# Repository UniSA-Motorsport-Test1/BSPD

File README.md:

View this project on [CADLAB.io](https://cadlab.io/project/26523). 

# BSPD

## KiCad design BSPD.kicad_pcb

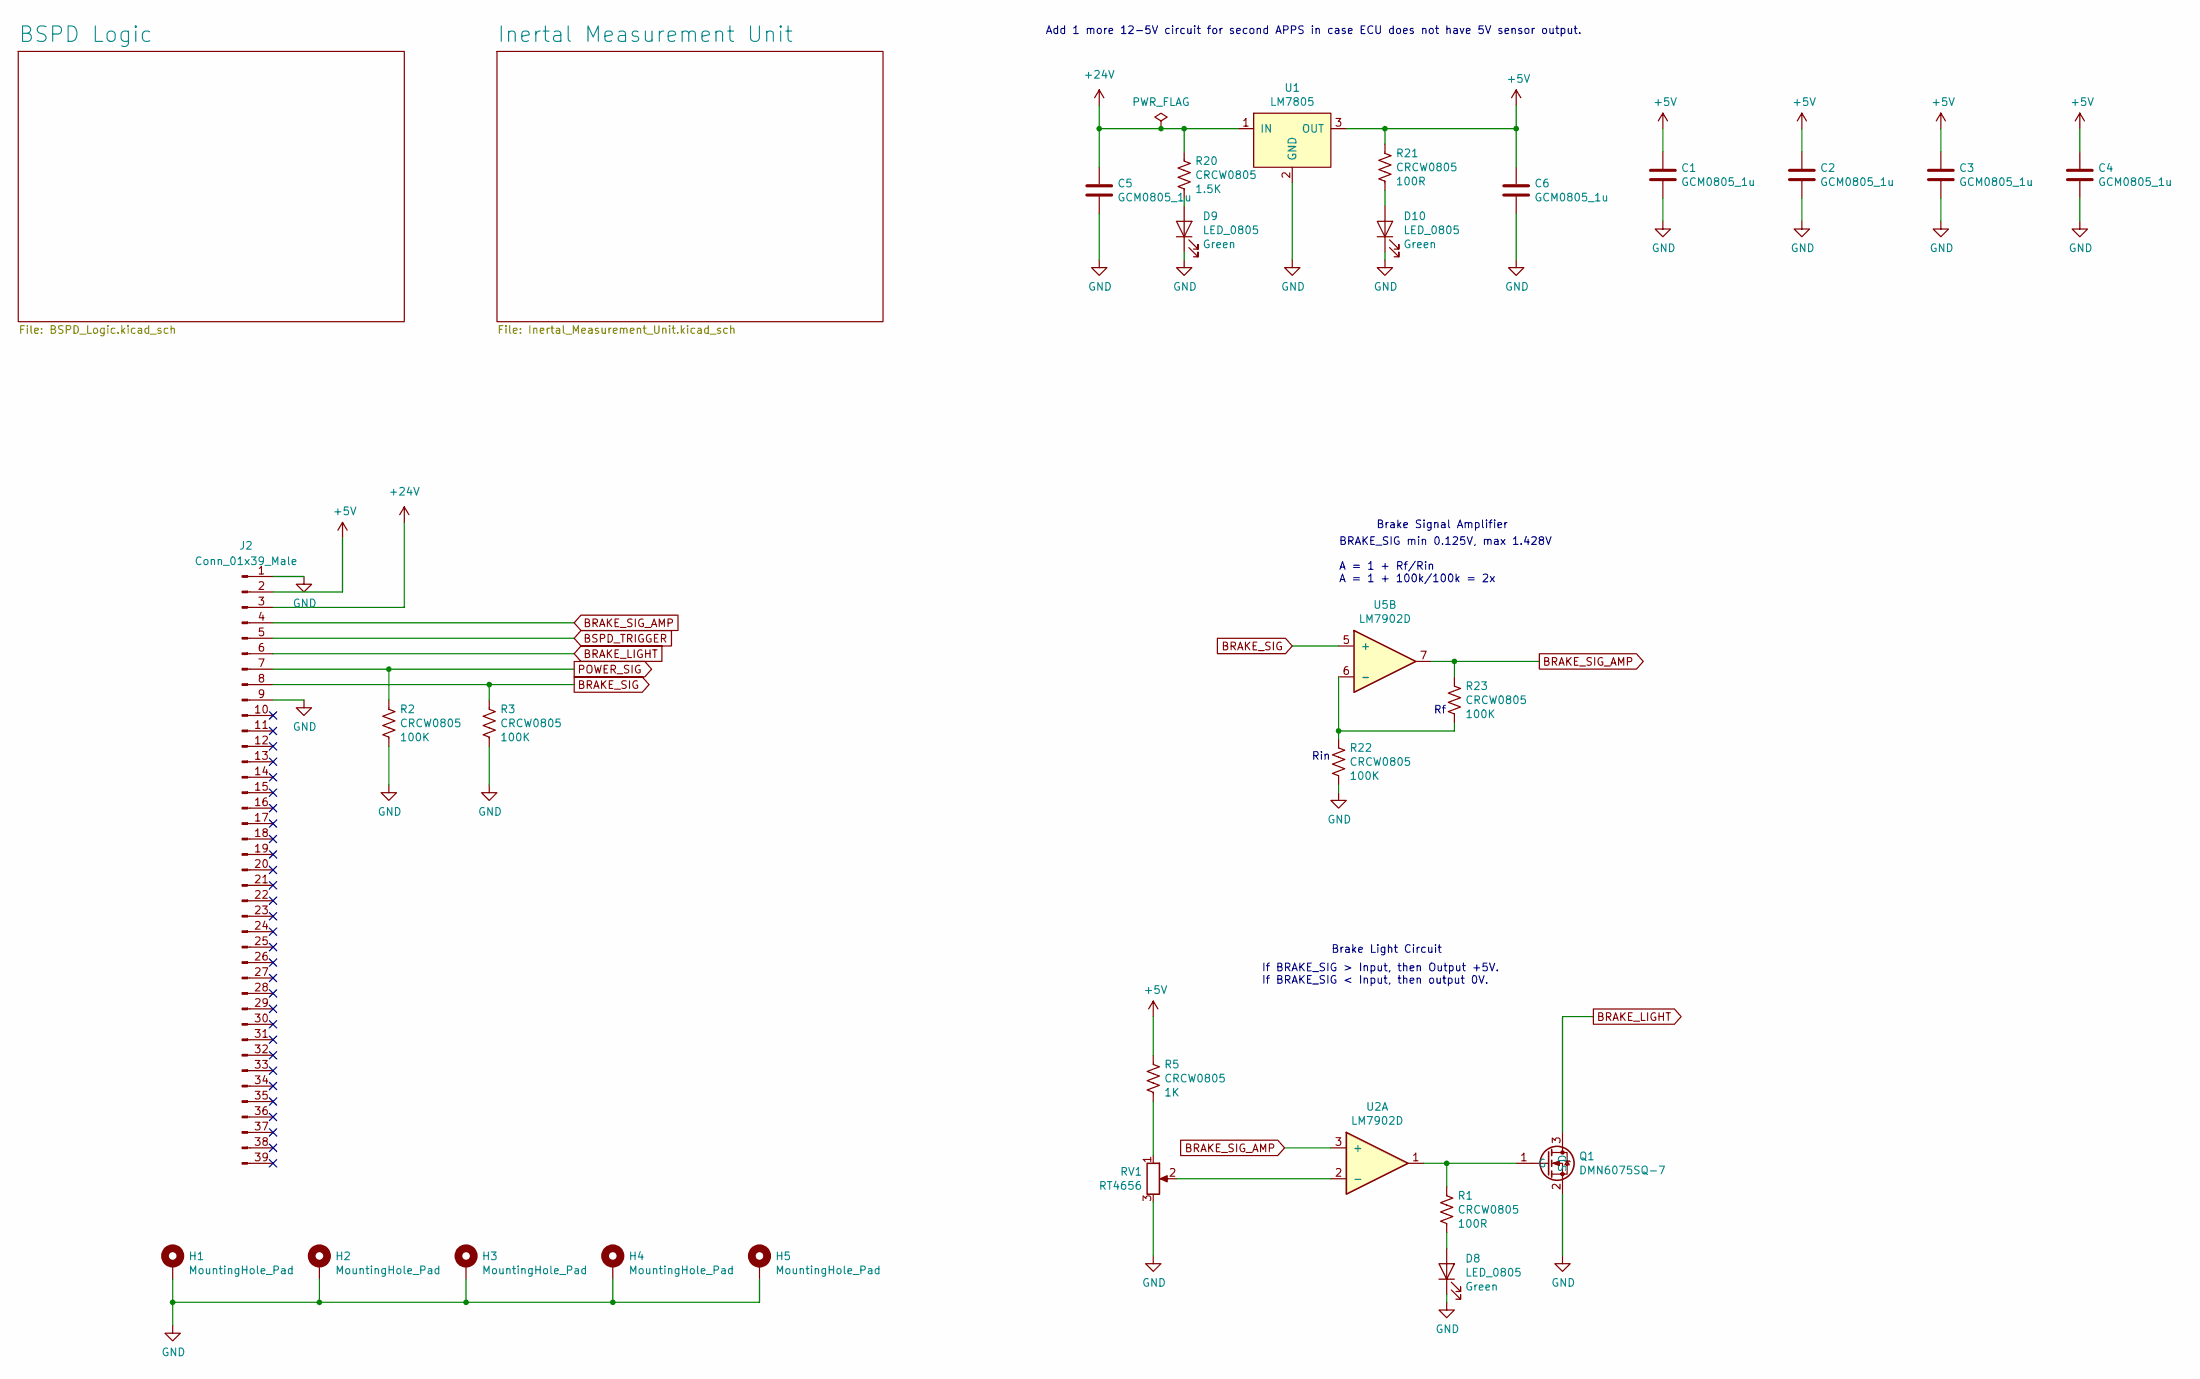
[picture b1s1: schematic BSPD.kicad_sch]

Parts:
C1, C2, C3, C4, C5, C6: GCM0805_1u; 0805; Voltage Rating 50V
D8, D9, D10: LED_0805; 0805
H1, H2, H3, H4, H5: MountingHole_Pad; MountingHole_3.2mm_M3_Pad_Via
J2: Conn_01x39_Male; Samtec_MECF-40-0_-L-DV_2x40_P1.27mm_Polarized_Edge
Q1: DMN6075SQ-7; SOT-23-3
R1, R2, R3, R5, R20, R21, R22, R23: CRCW0805; 0805; Voltage Rating 150V; Power Rating 125mW
RV1: RT4656; PinHeader_1x03_P2.54mm_Vertical
U1: LM7805; SOT-223-4; Current Rating 1.5A
U2, U5: LM7902D; SOIC-14

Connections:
+5V: C1.1, C2.1, C3.1, C4.1, C6.1, J2.2, R5.1, R21.1, U1.3 (OUT); also elsewhere on the board
+24V: C5.1, J2.3, R20.1, U1.1 (IN); also elsewhere on the board
BRAKE_LIGHT: J2.6, Q1.3 (D)
BRAKE_SIG: J2.8, R3.1, U5.5 (+)
BRAKE_SIG_AMP: J2.4, R23.1, U2.3 (+), U5.7; also elsewhere on the board
BSPD_TRIGGER: J2.5; also elsewhere on the board
GND: C1.2, C2.2, C3.2, C4.2, C5.2, C6.2, D8.1 (K), D9.1 (K), D10.1 (K), H1.1, H2.1, H3.1, H4.1, H5.1, J2.1, J2.9, Q1.2 (S), R2.2, R3.2, R22.2, RV1.3, U1.2 (GND); also elsewhere on the board
unnamed: D8.2 (A), R1.2
unnamed: D9.2 (A), R20.2
unnamed: D10.2 (A), R21.2
unnamed: Q1.1 (G), R1.1, U2.1
unnamed: R5.2, RV1.1
unnamed: R22.1, R23.2, U5.6 (-)
unnamed: RV1.2, U2.2 (-)
POWER_SIG: J2.7, R2.1; also elsewhere on the board

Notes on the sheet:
Rin
Brake Signal Amplifier
Add 1 more 12-5V circuit for second APPS in case ECU does not have 5V sensor output.
Brake Light Circuit
BRAKE_SIG min 0.125V, max 1.428V A = 1 + Rf/Rin A = 1 + 100k/100k = 2x
If BRAKE_SIG > Input, then Output +5V. If BRAKE_SIG < Input, then output 0V.

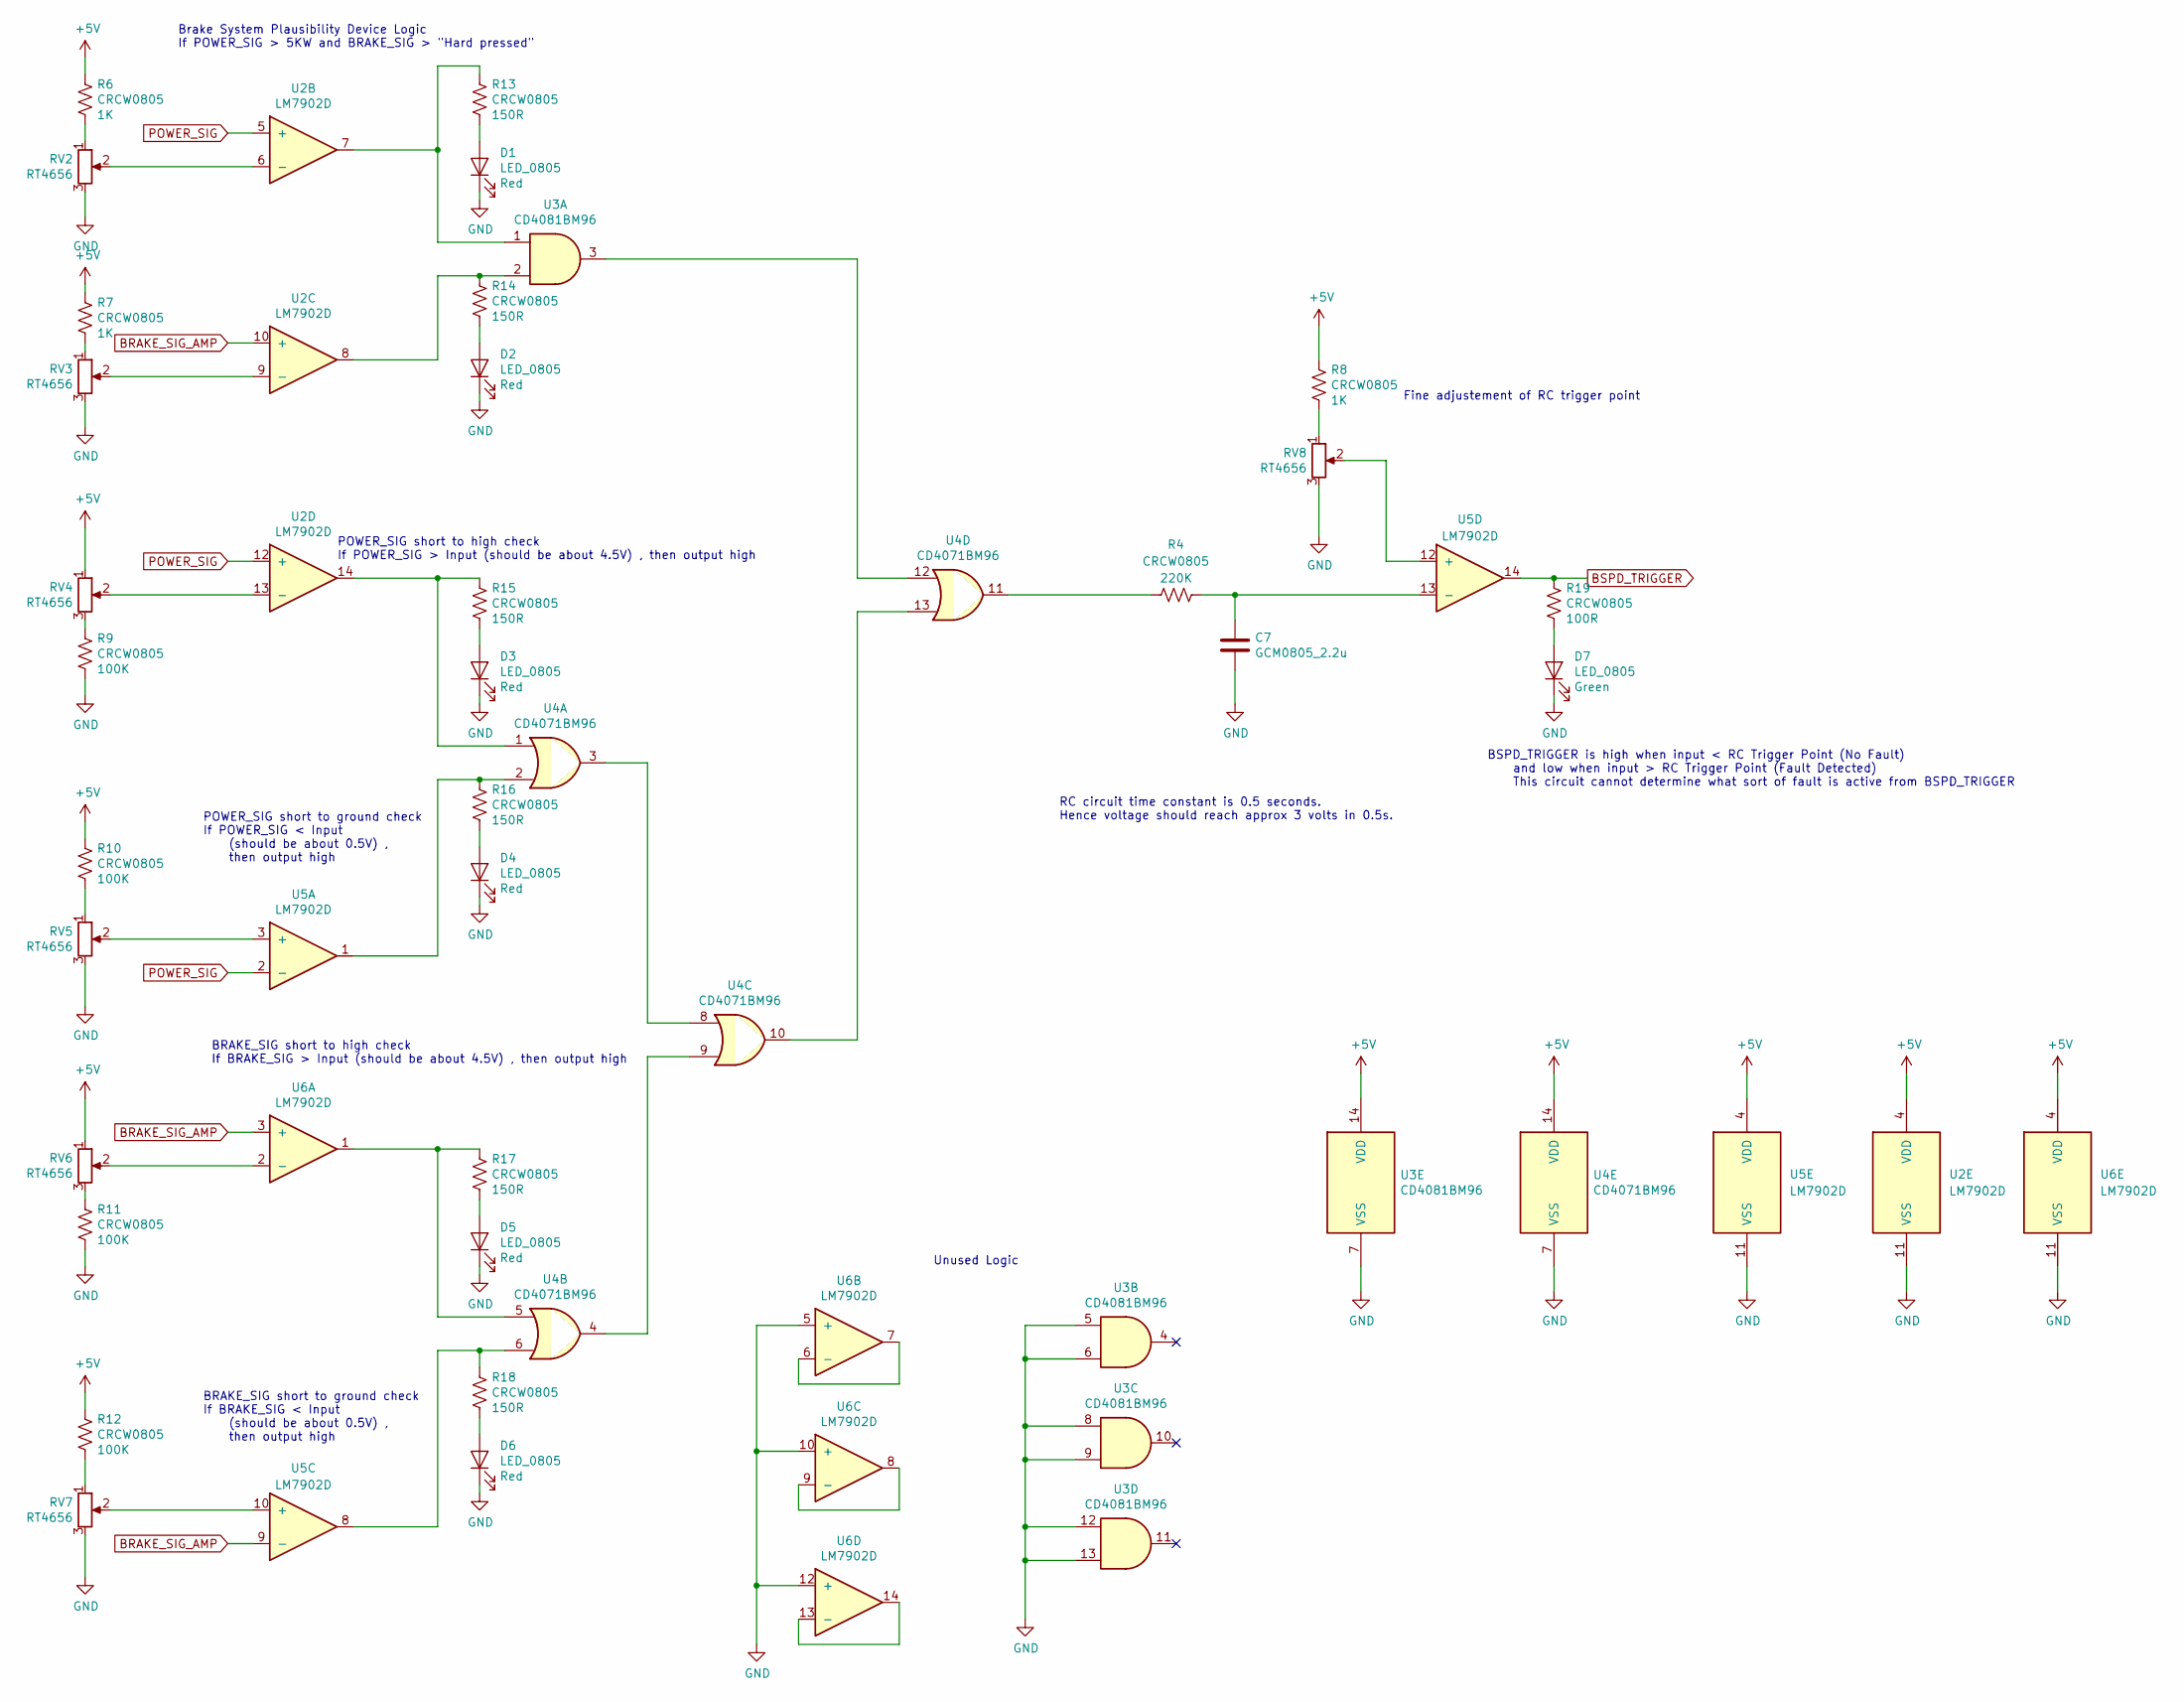
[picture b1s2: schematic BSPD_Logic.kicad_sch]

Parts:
C7: GCM0805_2.2u; 0805; Voltage Rating 16V
D1, D2, D3, D4, D5, D6, D7: LED_0805; 0805
R4, R6, R7, R8, R9, R10, R11, R12, R13, R14, R15, R16, R17, R18, R19: CRCW0805; 0805; Voltage Rating 150V; Power Rating 125mW
RV2, RV3, RV4, RV5, RV6, RV7, RV8: RT4656; PinHeader_1x03_P2.54mm_Vertical
U2, U5, U6: LM7902D; SOIC-14
U3: CD4081BM96; SOIC-14
U4: CD4071BM96; SOIC-14

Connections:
+5V: R6.1, R7.1, R8.1, R10.1, R12.1, RV4.1, RV6.1, U2.4 (VDD), U3.14 (VDD), U4.14 (VDD), U5.4 (VDD), U6.4 (VDD); also elsewhere on the board
BRAKE_SIG_AMP: U2.10 (+), U5.9 (-), U6.3 (+); also elsewhere on the board
BSPD_TRIGGER: R19.1, U5.14; also elsewhere on the board
GND: C7.2, D1.1 (K), D2.1 (K), D3.1 (K), D4.1 (K), D5.1 (K), D6.1 (K), D7.1 (K), R9.2, R11.2, RV2.3, RV3.3, RV5.3, RV7.3, RV8.3, U2.11 (VSS), U3.5, U3.6, U3.7 (VSS), U3.8, U3.9, U3.12, U3.13, U4.7 (VSS), U5.11 (VSS), U6.5 (+), U6.10 (+), U6.11 (VSS), U6.12 (+); also elsewhere on the board
unnamed: C7.1, R4.2, U5.13 (-)
unnamed: D1.2 (A), R13.2
unnamed: D2.2 (A), R14.2
unnamed: D3.2 (A), R15.2
unnamed: D4.2 (A), R16.2
unnamed: D5.2 (A), R17.2
unnamed: D6.2 (A), R18.2
unnamed: D7.2 (A), R19.2
unnamed: R4.1, U4.11
unnamed: R6.2, RV2.1
unnamed: R7.2, RV3.1
unnamed: R8.2, RV8.1
unnamed: R9.1, RV4.3
unnamed: R10.2, RV5.1
unnamed: R11.1, RV6.3
unnamed: R12.2, RV7.1
unnamed: R13.1, U2.7, U3.1
unnamed: R14.1, U2.8, U3.2
unnamed: R15.1, U2.14, U4.1
unnamed: R16.1, U4.2, U5.1
unnamed: R17.1, U4.5, U6.1
unnamed: R18.1, U4.6, U5.8
unnamed: RV2.2, U2.6 (-)
unnamed: RV3.2, U2.9 (-)
unnamed: RV4.2, U2.13 (-)
unnamed: RV5.2, U5.3 (+)
unnamed: RV6.2, U6.2 (-)
unnamed: RV7.2, U5.10 (+)
unnamed: RV8.2, U5.12 (+)
unnamed: U3.3, U4.12
unnamed: U4.3, U4.8
unnamed: U4.4, U4.9
unnamed: U4.10, U4.13
unnamed: U6.6 (-), U6.7
unnamed: U6.8, U6.9 (-)
unnamed: U6.13 (-), U6.14
POWER_SIG: U2.5 (+), U2.12 (+), U5.2 (-); also elsewhere on the board

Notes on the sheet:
POWER_SIG short to high check If POWER_SIG > Input (should be about 4.5V) , then output high
POWER_SIG short to ground check If POWER_SIG < Input (should be about 0.5V) , then output high
Fine adjustement of RC trigger point
BRAKE_SIG short to ground check If BRAKE_SIG < Input (should be about 0.5V) , then output high
RC circuit time constant is 0.5 seconds. Hence voltage should reach approx 3 volts in 0.5s.
Brake System Plausibility Device Logic If POWER_SIG > 5KW and BRAKE_SIG > "Hard pressed"
BSPD_TRIGGER is high when input < RC Trigger Point (No Fault) and low when input > RC Trigger Point (Fault Detected) This circuit cannot determine what sort of fault is active from BSPD_TRIGGER
BRAKE_SIG short to high check If BRAKE_SIG > Input (should be about 4.5V) , then output high
Unused Logic

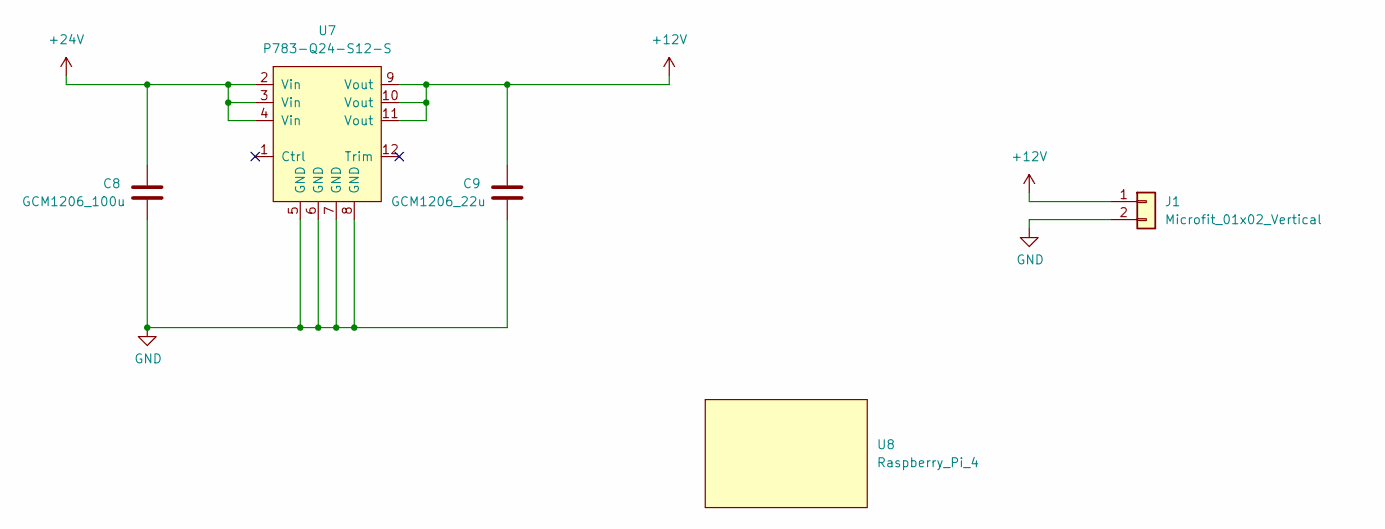
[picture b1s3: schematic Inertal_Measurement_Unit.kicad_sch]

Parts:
C8: GCM1206_100u; CP_Radial_D10.0mm_P5.00mm; Voltage Rating 50V
C9: GCM1206_22u; 1206; Voltage Rating 25V
J1: Microfit_01x02_Vertical; Molex_Micro-Fit_43650-0215_1x02_Vertical
U7: P783-Q24-S12-S
U8: Raspberry_Pi_4; Raspberry PI 4

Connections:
+12V: C9.1, J1.1, U7.9 (Vout), U7.10 (Vout), U7.11 (Vout)
+24V: C8.1, U7.2 (Vin), U7.3 (Vin), U7.4 (Vin); also elsewhere on the board
GND: C8.2, C9.2, J1.2, U7.5 (GND), U7.6 (GND), U7.7 (GND), U7.8 (GND); also elsewhere on the board

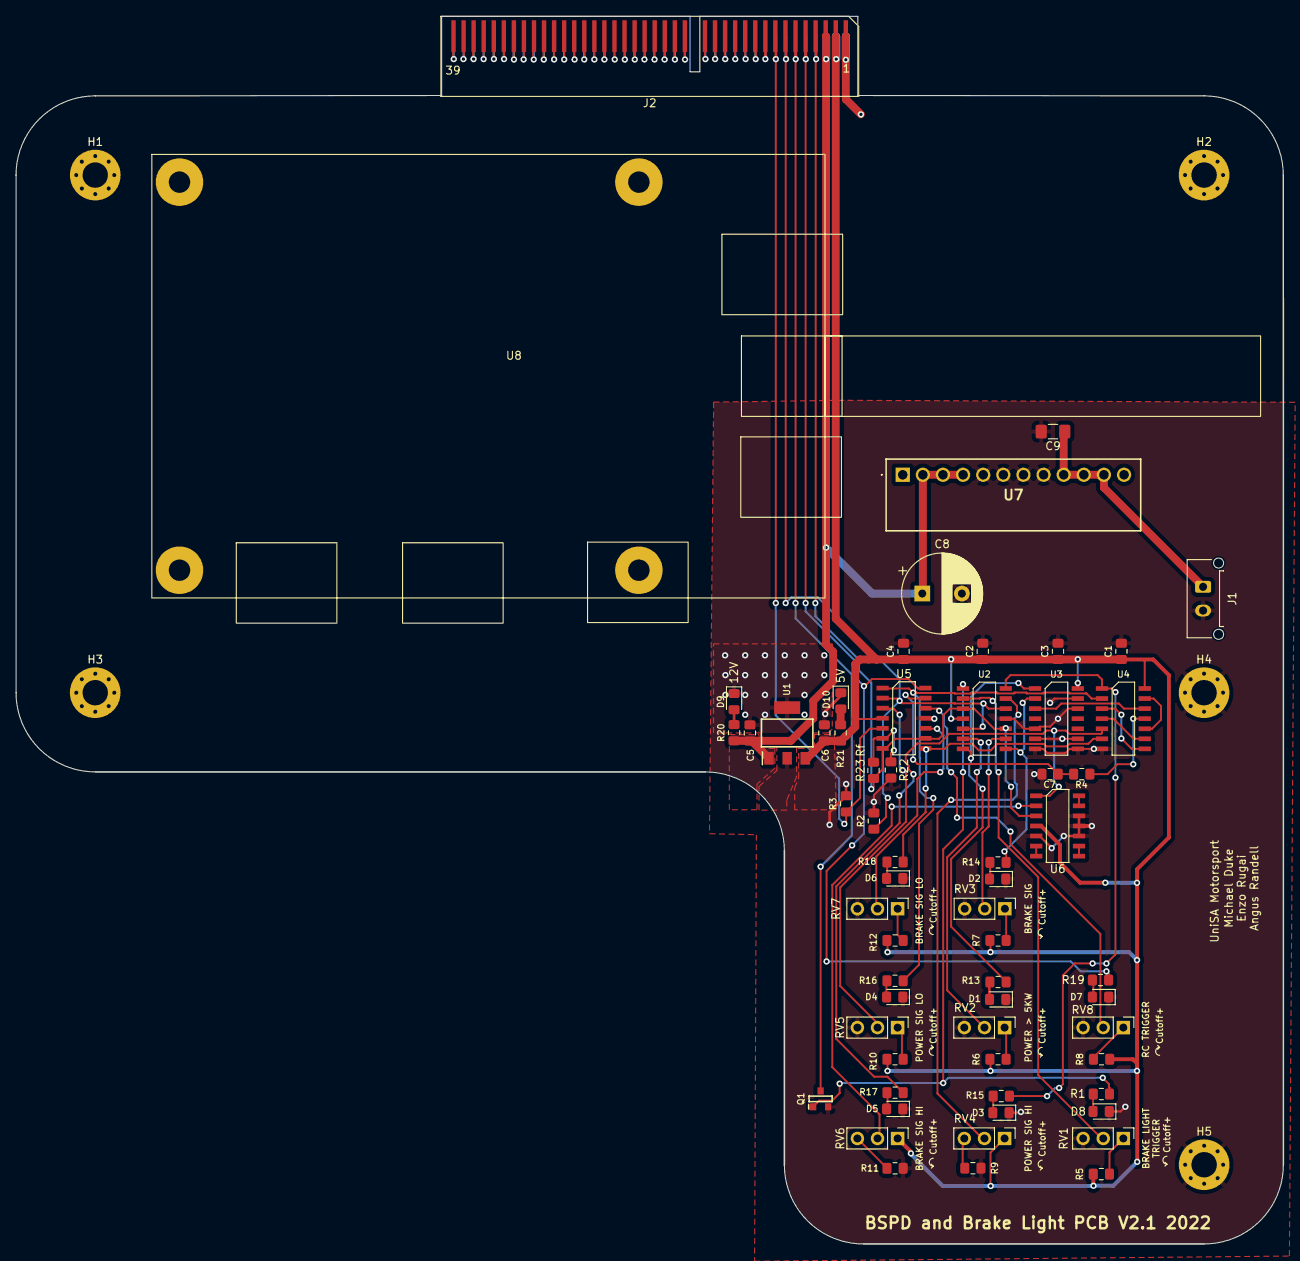
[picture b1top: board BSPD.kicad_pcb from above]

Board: 2 copper layers, 160.0 x 155.0 mm, 66 parts (0 on the bottom side), 52 nets.

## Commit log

2023-02-16 Added BSPD Files
2023-02-16 Backlink to CADLAB.io has been added.
2023-02-21 Switched D7 and R19 with D3 and R15
2023-02-21 made traces the correct width
2023-02-28 The ground rale has been modifed so now it is not where the rasberry pie will be mounted which should stop it from shorting to ground
